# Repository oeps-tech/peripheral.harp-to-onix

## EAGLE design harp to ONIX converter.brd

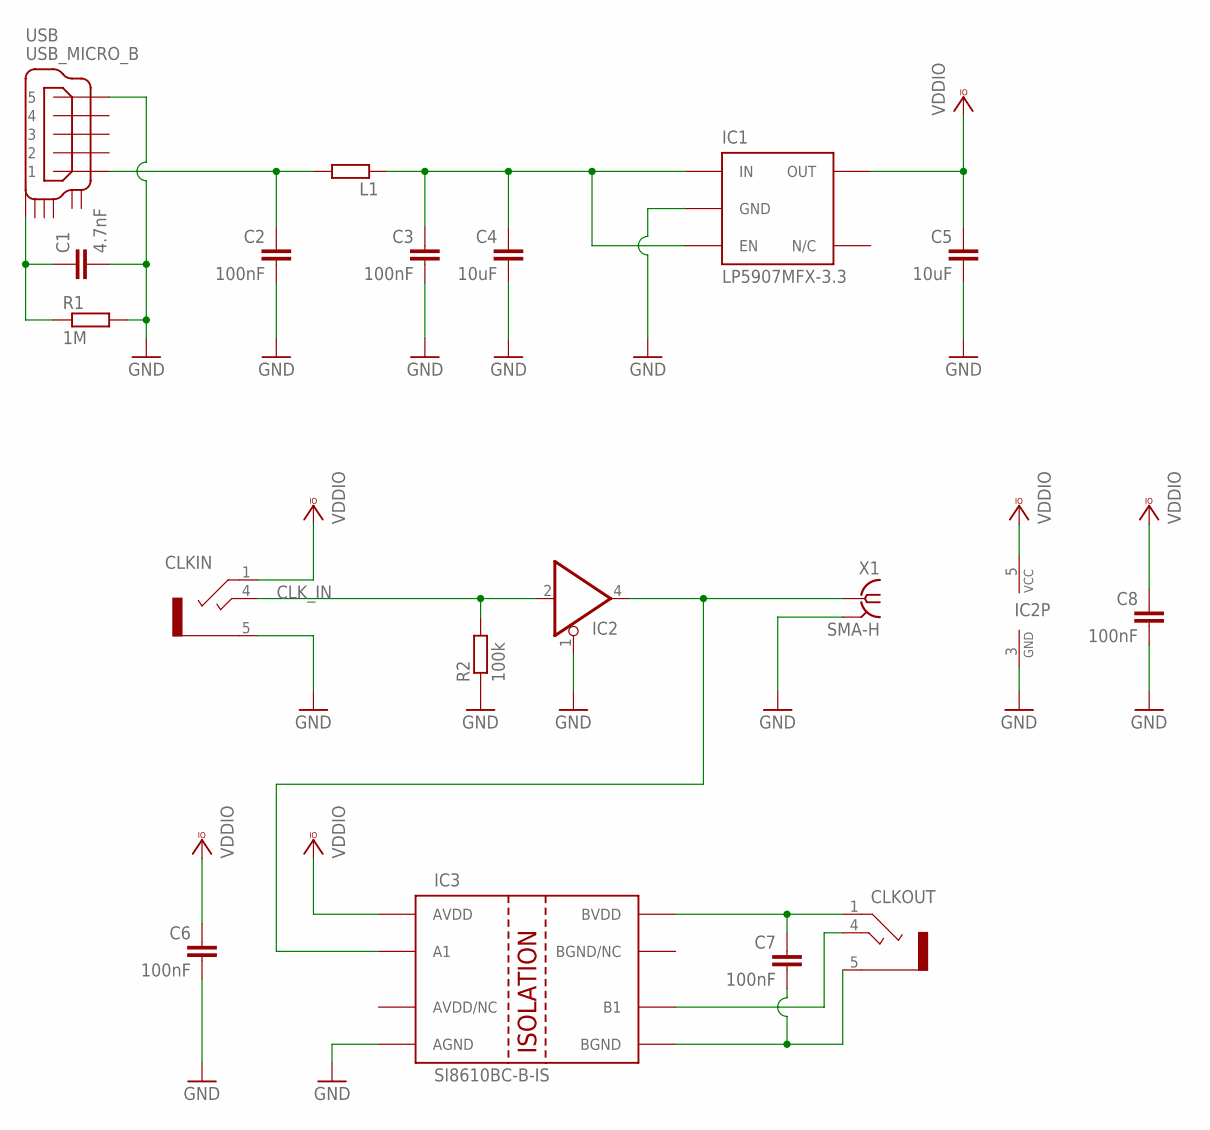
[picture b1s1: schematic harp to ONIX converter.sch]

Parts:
C1: 4.7nF; C0402
C2, C3, C6, C8: 100nF; C0402
C4, C5: 10uF; C0603
C7: 100nF; C0402; MPN MC0402B104K160CT
CLKIN: STEREO_JACK; 35RASMT2BHNTRX
CLKOUT: CLCK_JACK; 35RASMT2BHNTRX; MPN 35RASMT2BHNTRX
IC1: LP5907MFX-3.3; TSOT23-5
IC2: 74AHC1G125DBV; SOT23-5
IC3: SI8610BC-B-IS; SO-08; MPN SI8610EC-B-IS
L1: ???; R0805
R1: 1M; R0402
R2: 100k; R0402
USB: USB_MICRO_B; ZX62D-B-5P8
X1: SMA-H; BU-SMA-V

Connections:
5V_RAW: C3.1, C4.1, IC1.1 (IN), IC1.3 (EN), L1.1
CLK_IN: CLKIN.4, IC2.2 (I), R2.2
GND: C1.2, C2.2, C3.2, C4.2, C5.2, C6.2, C8.2, CLKIN.5, IC1.2 (GND), IC2.1 (OE), IC2.3 (GND), IC3.4 (AGND), R1.2, R2.1, USB.P$5 (5), X1.2, X1.3 (2), X1.4 (2), X1.5 (2)
GND_ISO: C7.2, CLKOUT.5, IC3.5 (BGND)
unnamed: IC2.4 (O), IC3.2 (A1), X1.1
unnamed: CLKOUT.4, IC3.6 (B1)
unnamed: C7.1, CLKOUT.1, IC3.8 (BVDD)
unnamed: C2.1, L1.2, USB.P$1 (1)
unnamed: C1.1, R1.1, USB.SHIELD_4
VCCIO: C5.1, C6.1, C8.1, CLKIN.1, IC1.5 (OUT), IC2.5 (VCC), IC3.1 (AVDD)

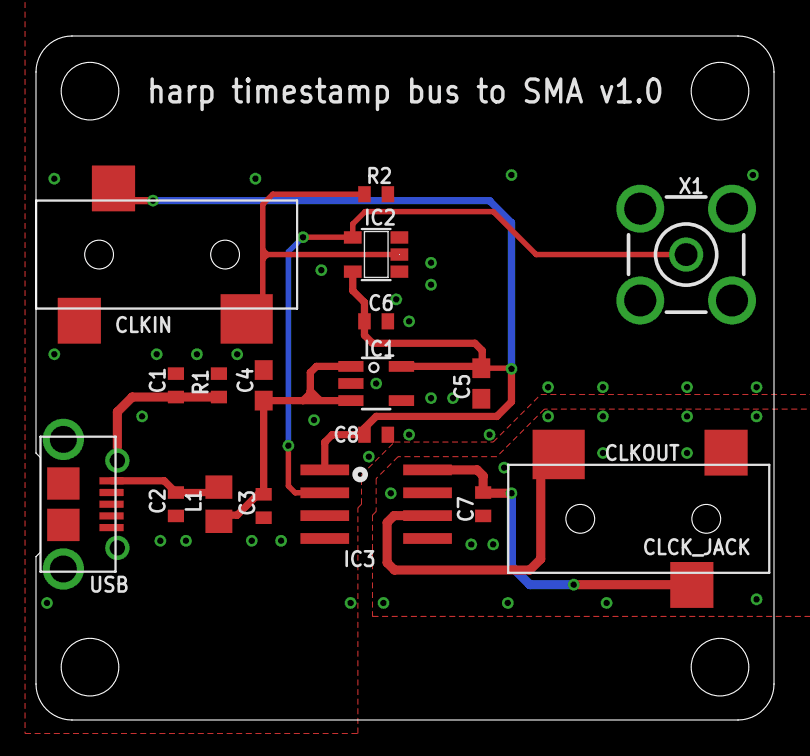
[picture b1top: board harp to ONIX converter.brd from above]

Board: 2 copper layers, 41.0 x 38.0 mm, 18 parts (0 on the bottom side), 10 nets.

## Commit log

2023-09-25 Added PCB files.
2023-09-25 Added BOM.
2023-09-25 Added production files.
2023-09-25 Added photos.
2023-09-28 Replaced some BOM items with available components.
